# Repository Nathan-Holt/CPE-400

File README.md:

This holds files for the PCB and the CAD files for the Fetch Me Their Soles Capstone Project + CPE 400 capstone extension

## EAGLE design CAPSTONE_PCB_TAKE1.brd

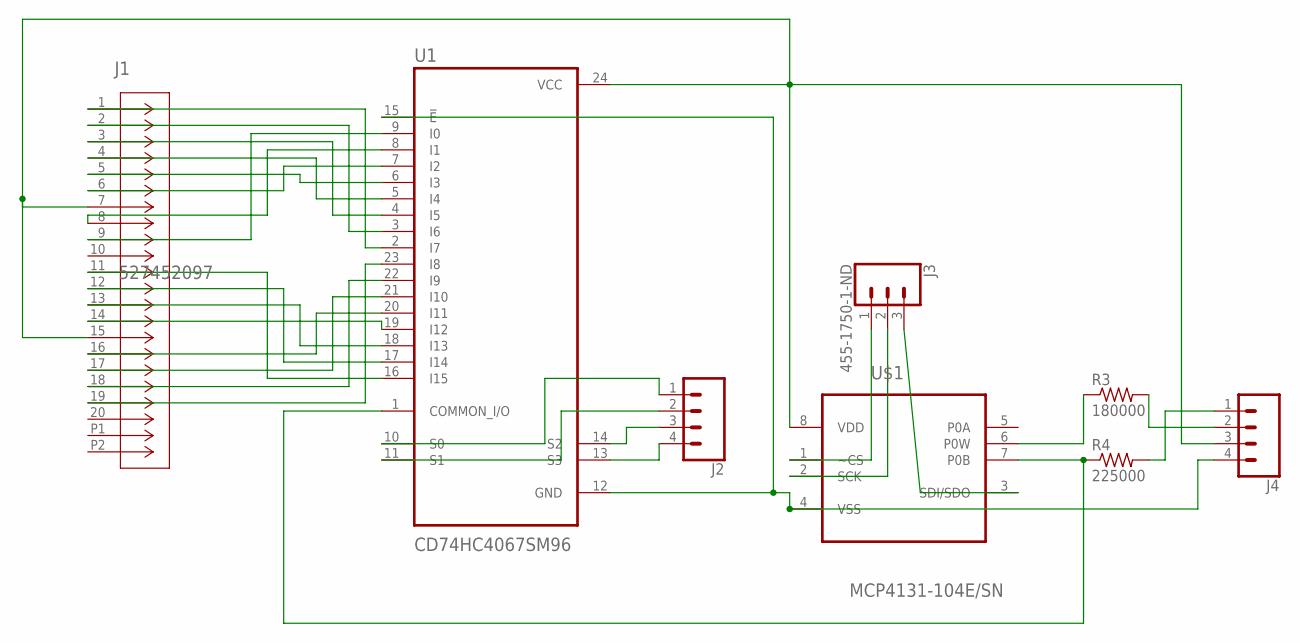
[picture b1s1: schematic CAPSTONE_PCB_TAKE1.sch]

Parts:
J1: 527452097; CON_527452097_MOL
J2, J4: CONN_04LOCK; 1X04_LOCK
J3: 455-1750-1-ND; 1X03
R3: 180000; 0204V
R4: 225000; 0204V
U1: CD74HC4067SM96; SOP65P780X200-24N
U$1: MCP4131-104E/SN; SOIC127P600X175-8N

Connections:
unnamed: J1.1, U1.2 (I7)
unnamed: J1.2, U1.3 (I6)
unnamed: J1.3, U1.4 (I5)
unnamed: J1.4, U1.5 (I4)
unnamed: J1.5, U1.6 (I3)
unnamed: J1.6, U1.7 (I2)
unnamed: J1.8, U1.8 (I1)
unnamed: J1.9, U1.9 (I0)
unnamed: J1.19, U1.23 (I8)
unnamed: J1.18, U1.22 (I9)
unnamed: J1.17, U1.21 (I10)
unnamed: J1.16, U1.20 (I11)
unnamed: J1.14, U1.19 (I12)
unnamed: J1.13, U1.18 (I13)
unnamed: J1.12, U1.17 (I14)
unnamed: J1.11, U1.16 (I15)
unnamed: R4.1, U1.1 (COMMON_I/O), U$1.7 (P0B)
unnamed: R3.1, U$1.6 (P0W)
unnamed: J3.1, U$1.1 (~CS)
unnamed: J3.2, U$1.2 (SCK)
unnamed: J3.3, U$1.3 (SDI/SDO)
unnamed: J4.2, R3.2
unnamed: J4.1, R4.2
unnamed: J2.4, U1.13 (S3)
unnamed: J2.3, U1.14 (S2)
unnamed: J2.2, U1.11 (S1)
unnamed: J2.1, U1.10 (S0)
unnamed: J4.4, U1.12 (GND), U1.15 (!E), U$1.4 (VSS)
VIN(3.3V): J1.7, J1.15, J4.3, U1.24 (VCC), U$1.8 (VDD)

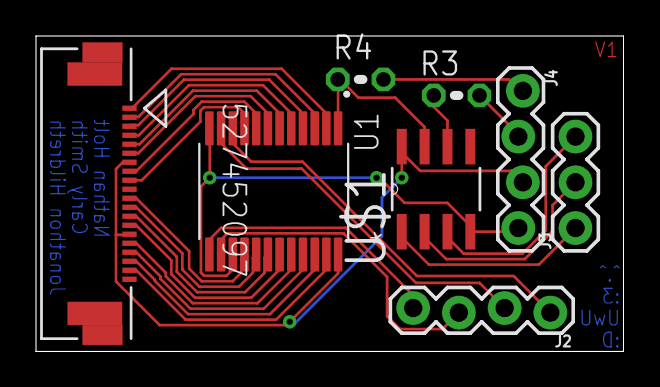
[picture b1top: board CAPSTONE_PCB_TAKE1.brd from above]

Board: 2 copper layers, 32.6 x 17.5 mm, 8 parts (0 on the bottom side), 29 nets.

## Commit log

2025-12-10 CAD files for the insole.
    Forgive me for the state of these. I did not have the care to make them pretty, i just kept editing the same overworked model

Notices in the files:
parts and their libraries:
SparkFun-Connectors: Licensing: Creative Commons ShareAlike 4.0 International - https://creativecommons.org/licenses/by-sa/4.0
